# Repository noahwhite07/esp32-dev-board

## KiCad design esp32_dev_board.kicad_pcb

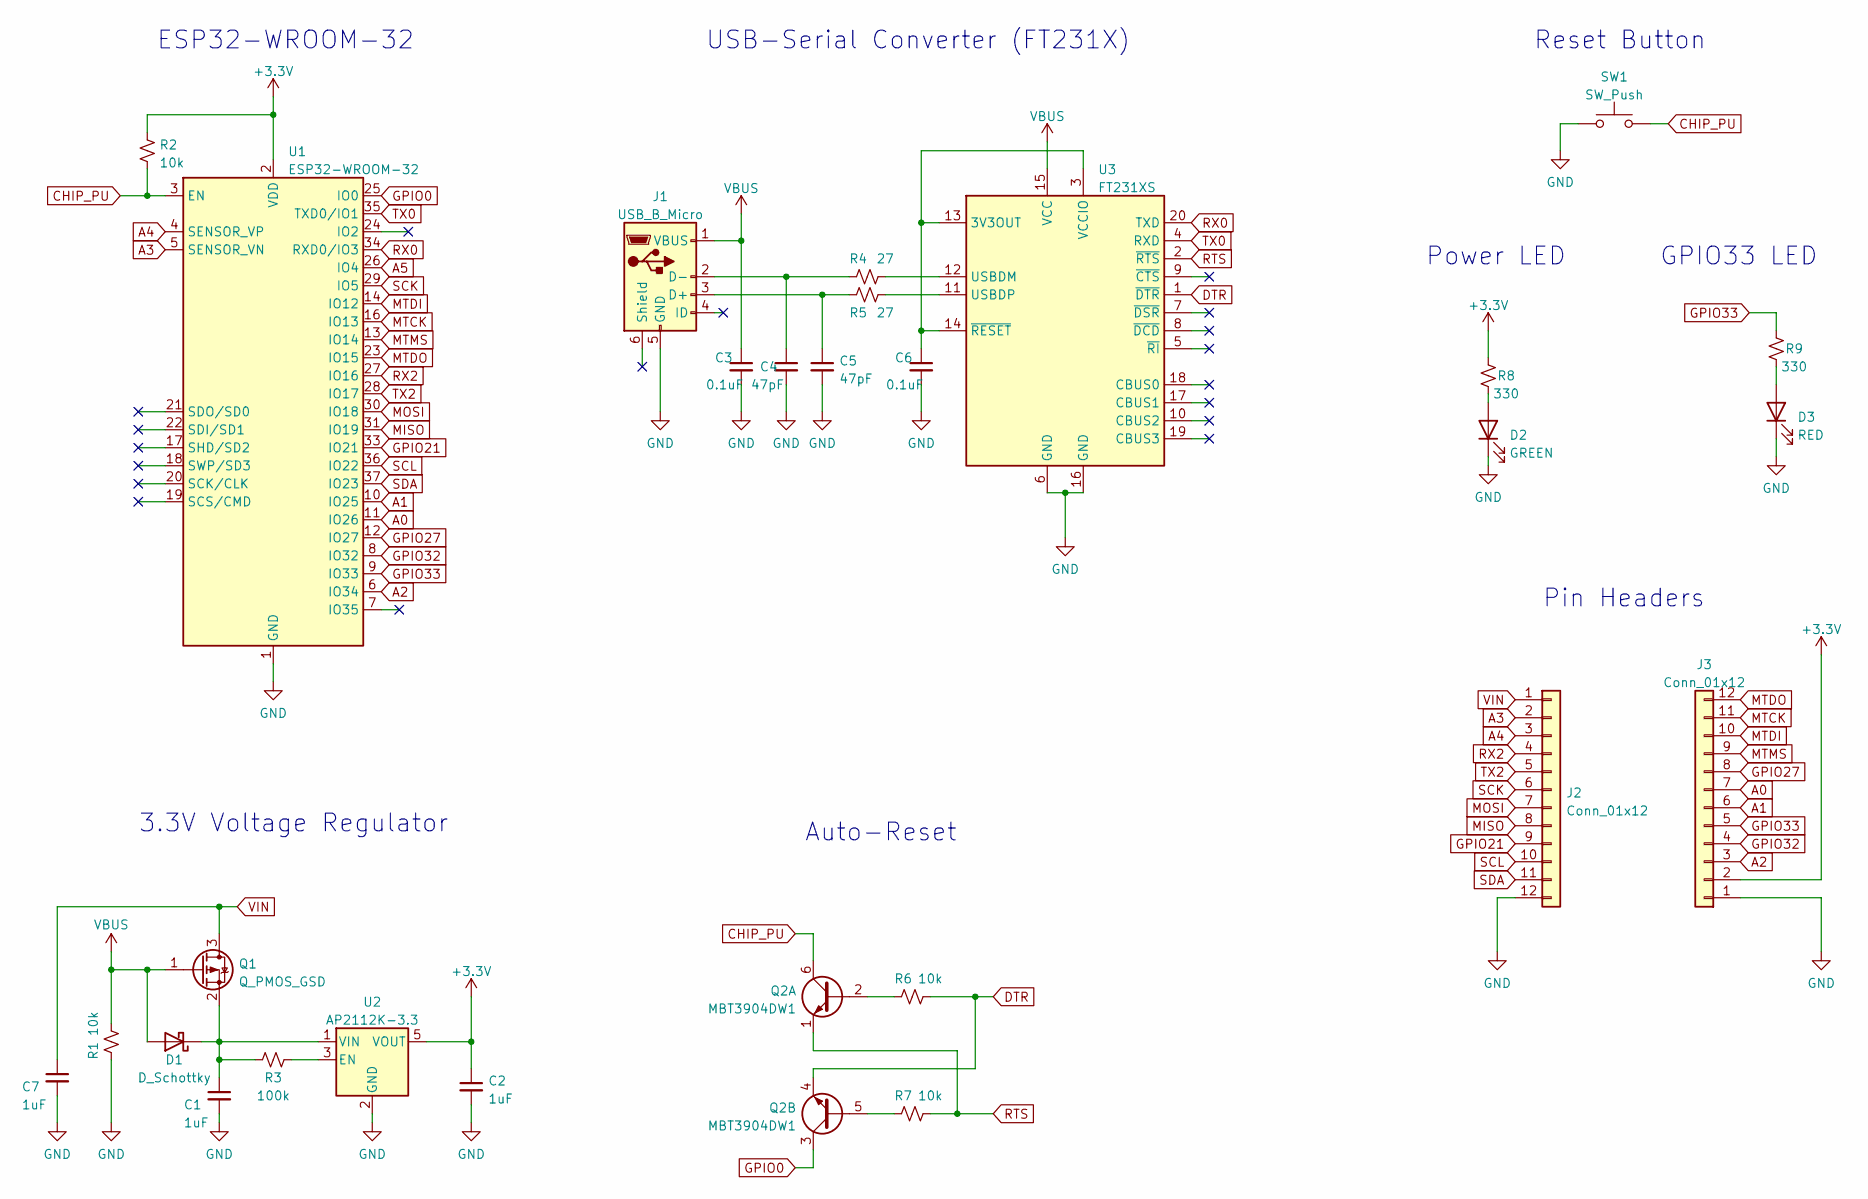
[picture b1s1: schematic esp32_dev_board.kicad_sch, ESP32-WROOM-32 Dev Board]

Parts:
C1, C2, C7: 1uF; C_0805_2012Metric_Pad1.18x1.45mm_HandSolder
C3, C6: 0.1uF; C_0805_2012Metric_Pad1.18x1.45mm_HandSolder
C4, C5: 47pF; C_0805_2012Metric_Pad1.18x1.45mm_HandSolder
D1: D_Schottky; D_SOD-123
D2: GREEN; LED_0805_2012Metric_Pad1.15x1.40mm_HandSolder
D3: RED; LED_0805_2012Metric_Pad1.15x1.40mm_HandSolder
J1: USB_B_Micro; USB_Micro-B_GCT_USB3076-30-A
J2, J3: Conn_01x12; PinHeader_1x12_P2.54mm_Vertical
Q1: Q_PMOS_GSD; SOT-23
Q2: MBT3904DW1; SOT-363_SC-70-6_Handsoldering
R1, R2, R6, R7: 10k; R_0805_2012Metric_Pad1.20x1.40mm_HandSolder
R3: 100k; R_0805_2012Metric_Pad1.20x1.40mm_HandSolder
R4, R5: 27; R_0805_2012Metric_Pad1.20x1.40mm_HandSolder
R8, R9: 330; R_0805_2012Metric_Pad1.20x1.40mm_HandSolder
SW1: SW_Push; SW_Tactile_SPST_NO_Straight_CK_PTS636Sx25SMTRLFS
U1: ESP32-WROOM-32
U2: AP2112K-3.3; SOT-23-5
U3: FT231XS; SSOP-20_3.9x8.7mm_P0.635mm

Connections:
+3.3V: C2.1, J3.2, R2.1, R8.2, U1.2 (VDD), U2.5 (VOUT)
A0: J3.7, U1.11 (IO26)
A1: J3.6, U1.10 (IO25)
A2: J3.3, U1.6 (IO34)
A3: J2.2, U1.5 (SENSOR_VN)
A4: J2.3, U1.4 (SENSOR_VP)
A5: U1.26 (IO4)
CHIP_PU: Q2.6 (C1), R2.2, SW1.2, U1.3 (EN)
DTR: Q2.4 (E2), R6.1, U3.1 (~DTR)
GND: C1.2, C2.2, C3.2, C4.2, C5.2, C6.2, C7.2, D2.1 (K), D3.1 (K), J1.5 (GND), J2.12, J3.1, R1.2, SW1.1, U1.1 (GND), U1.15 (GND), U1.38 (GND), U1.39 (GND), U2.2 (GND), U3.6 (GND), U3.16 (GND)
GPIO0: Q2.3 (C2), U1.25 (IO0)
GPIO21: J2.9, U1.33 (IO21)
GPIO27: J3.8, U1.12 (IO27)
GPIO32: J3.4, U1.8 (IO32)
GPIO33: J3.5, R9.2, U1.9 (IO33)
MISO: J2.8, U1.31 (IO19)
MOSI: J2.7, U1.30 (IO18)
MTCK: J3.11, U1.16 (IO13)
MTDI: J3.10, U1.14 (IO12)
MTDO: J3.12, U1.23 (IO15)
MTMS: J3.9, U1.13 (IO14)
unnamed: C1.1, D1.1 (K), Q1.2 (S), R3.2, U2.1 (VIN)
unnamed: C4.1, J1.2 (D-), R4.2
unnamed: C5.1, J1.3 (D+), R5.2
unnamed: C6.1, U3.3 (VCCIO), U3.13 (3V3OUT), U3.14 (~RESET)
unnamed: D2.2 (A), R8.1
unnamed: D3.2 (A), R9.1
unnamed: Q2.2 (B1), R6.2
unnamed: Q2.5 (B2), R7.2
unnamed: R3.1, U2.3 (EN)
unnamed: R4.1, U3.12 (USBDM)
unnamed: R5.1, U3.11 (USBDP)
RTS: Q2.1 (E1), R7.1, U3.2 (~RTS)
RX0: U1.34 (RXD0/IO3), U3.20 (TXD)
RX2: J2.4, U1.27 (IO16)
SCK: J2.6, U1.29 (IO5)
SCL: J2.10, U1.36 (IO22)
SDA: J2.11, U1.37 (IO23)
TX0: U1.35 (TXD0/IO1), U3.4 (RXD)
TX2: J2.5, U1.28 (IO17)
VBUS: C3.1, D1.2 (A), J1.1 (VBUS), Q1.1 (G), R1.1, U3.15 (VCC)
VIN: C7.1, J2.1, Q1.3 (D)

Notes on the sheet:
GPIO33 LED
USB-Serial Converter (FT231X)
Reset Button
3.3V Voltage Regulator
ESP32-WROOM-32
Auto-Reset
Pin Headers
Power LED

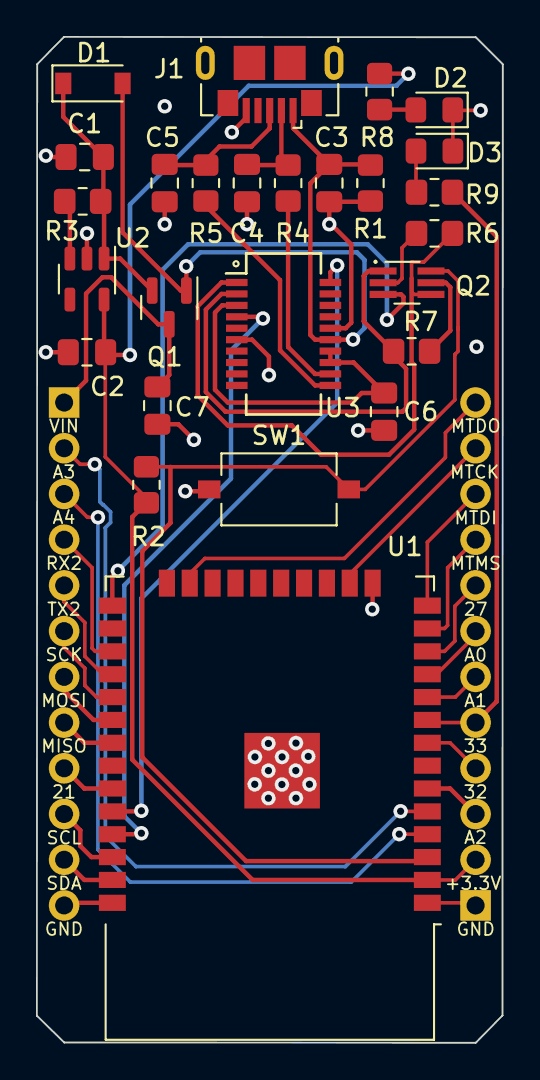
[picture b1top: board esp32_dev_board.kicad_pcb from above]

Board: 4 copper layers, 25.9 x 55.9 mm, 28 parts (0 on the bottom side), 41 nets.

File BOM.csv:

Source:,D:\Program Files\KiCad_6\projects\lipo_charger\lipo_charger.kicad_sch,,,,,,,,
Date:,2/9/2023 15:37,,,,,,,,
Tool:,Eeschema (6.0.10),,,,,,,,
Generator:,D:\Program Files\KiCad_6\bin\scripting\plugins/bom_csv_grouped_by_value.py,,,,,,,,
Component Count:,19,,,,,,,,
,,,,,,,,,
,,,,,,,,,
,,,,,,,,,
,,,,,,,,,
Collated Components:,,,,,,,,,
,,,,,,,,,
Item,Qty,Qty x3,Reference(s),Value,Link,Datasheet,Description,MPN,Price
1,3,9,"C1, C2, C7",1uF,https://www.mouser.com/ProductDetail/Samsung-Electro-Mechani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,~,,,
2,2,6,"C3, C6",0.1uF,https://www.mouser.com/ProductDetail/Samsung-Electro-Mechani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,~,,C0805C470J5GACTU,
3,2,6,"C4, C5",47pF,https://www.mouser.com/ProductDetail/KEMET/C0805C470J5GACTU?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,~,,,
4,1,3,D1,D_Schottky,https://www.mouser.com/ProductDetail/onsemi/NRVB120VLSFT1G?q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,~,,,
5,1,3,D2,GREEN,https://www.mouser.com/ProductDetail/Wurth-Elektronik/150080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,~,,,
6,1,3,D3,RED,https://www.mouser.com/ProductDetail/Wurth-Elektronik/150080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,~,,,
7,1,3,J1,USB_B_Micro,https://www.mouser.com/ProductDetail/GCT/USB3076-30-A?qs=KUo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,~,,,
8,2,6,"J2, J3",Conn_01x12,~,,,,
9,1,3,Q1,Q_PMOS_GSD,https://www.mouser.com/ProductDetail/Diodes-Incorporated/DMP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,~,,,
10,1,3,Q2,MBT3904DW1,https://www.mouser.com/ProductDetail/onsemi/MBT3904DW1T1G?qs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,~,,,
11,4,12,"R1, R2, R6, R7",10k,https://www.mouser.com/ProductDetail/Panasonic/ERJ-6ENF1002V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,~,,,
12,1,3,R3,100k,https://www.mouser.com/ProductDetail/Vishay-Dale/CRCW0805100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,~,,,
13,2,6,"R4, R5",27,https://www.mouser.com/ProductDetail/Bourns/CR0805-FX-27R0EL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,~,,,
14,2,6,"R8, R9",330,https://www.mouser.com/ProductDetail/YAGEO/RC0805FR-07332RL?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,~,,,
15,1,3,SW1,SW_Push,https://www.mouser.com/ProductDetail/CK/PTS636-SM25-SMTR-LFS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,~,,,
16,1,3,U1,ESP32-WROOM-32,https://www.mouser.com/ProductDetail/Espressif-Systems/ESP32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,~,,,
17,1,3,U2,AP2112K-3.3,https://www.mouser.com/ProductDetail/Diodes-Incorporated/AP2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,~,,,
18,1,3,U3,FT231XS,https://www.mouser.com/ProductDetail/FTDI/FT231XS-U?qs=Gp1Yz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,~,,,
,,,,,,,,,
,,,,,,,,,
,,,,,,,,Total,4.81
,,,,,,,,,
,,,,,,,,,
,,,,,,,,,
CL21A106KOQNNNE,1,,,,,,,,
CL21A475KPFNNNE,1,,,,,,,,
CL21F104ZBANNNC,1,,,,,,,,
150080VS75000,1,,,,,,,,
150080RS75000,1,,,,,,,,
USB3076-30-A,1,,,,,,,,
LQM21PN4R7MGRD,1,,,,,,,,
DMN2053UVT-7,1,,,,,,,,
AC0805FR-072KL,1,,,,,,,,
RC0805FR-07220RL,2,,,,,,,,
RC0805JR-071K1L,1,,,,,,,,
RC0805FR-07332RL,1,,,,,,,,
OS102011MA1QN1,1,,,,,,,,
MCP73831T-2DCI/OT,1,,,,,,,,
DIO6605BFN8,1,,,,,,,,
AP9101CK6-AYTRG1,1,,,,,,,,

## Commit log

2023-06-10 Change global labels TX and RX to TX0 and RX0
2023-06-10 Change to 4-layer board and finish routing
2023-06-12 Add silkscreen, round corners, and small fixes
2023-06-12 Change C2 value and add back silkscreen
2023-06-12 Fix serial connection between ESP32 and FT231X
2023-06-12 Generate Gerber files
2023-06-14 Generate Gerber files and BOM
